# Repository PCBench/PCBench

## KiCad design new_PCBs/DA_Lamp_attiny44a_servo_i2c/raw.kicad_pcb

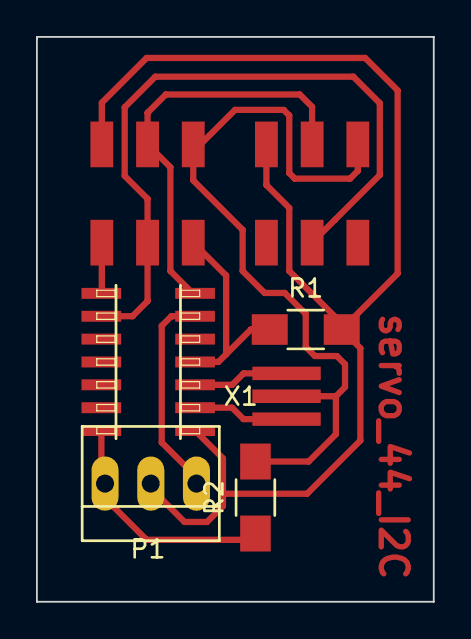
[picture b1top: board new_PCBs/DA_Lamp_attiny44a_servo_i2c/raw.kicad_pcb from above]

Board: 2 copper layers, 22.0 x 31.4 mm, 7 parts (0 on the bottom side), 9 nets.

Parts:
IC1: ATTINY44A-SS; fab-SOIC14
M1: AVRISP & I2C; fab-2X03SMD
M2: I2C; fab-2X03SMD
P1: CONN_01X03; PINHEAD1-3
R1: 10k; R_1206_HandSoldering
R2: 0; R_1206_HandSoldering
X1: CRYSTAL_SMD; Crystal_XC1109CT-ND

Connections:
+5V: IC1.1, M1.2, M2.2, P1.2, R1.2
/PA4: IC1.9, M1.3, M2.3
/PA5: IC1.8, M1.1
/PA6: IC1.7, M1.4, M2.4
/PA7: IC1.6, P1.1
/PB3: IC1.4, M1.5, R1.1
GND: IC1.14, M1.6, M2.6, P1.3, R2.1, R2.2, X1.2
unnamed: IC1.2, X1.3
unnamed: IC1.3, X1.1

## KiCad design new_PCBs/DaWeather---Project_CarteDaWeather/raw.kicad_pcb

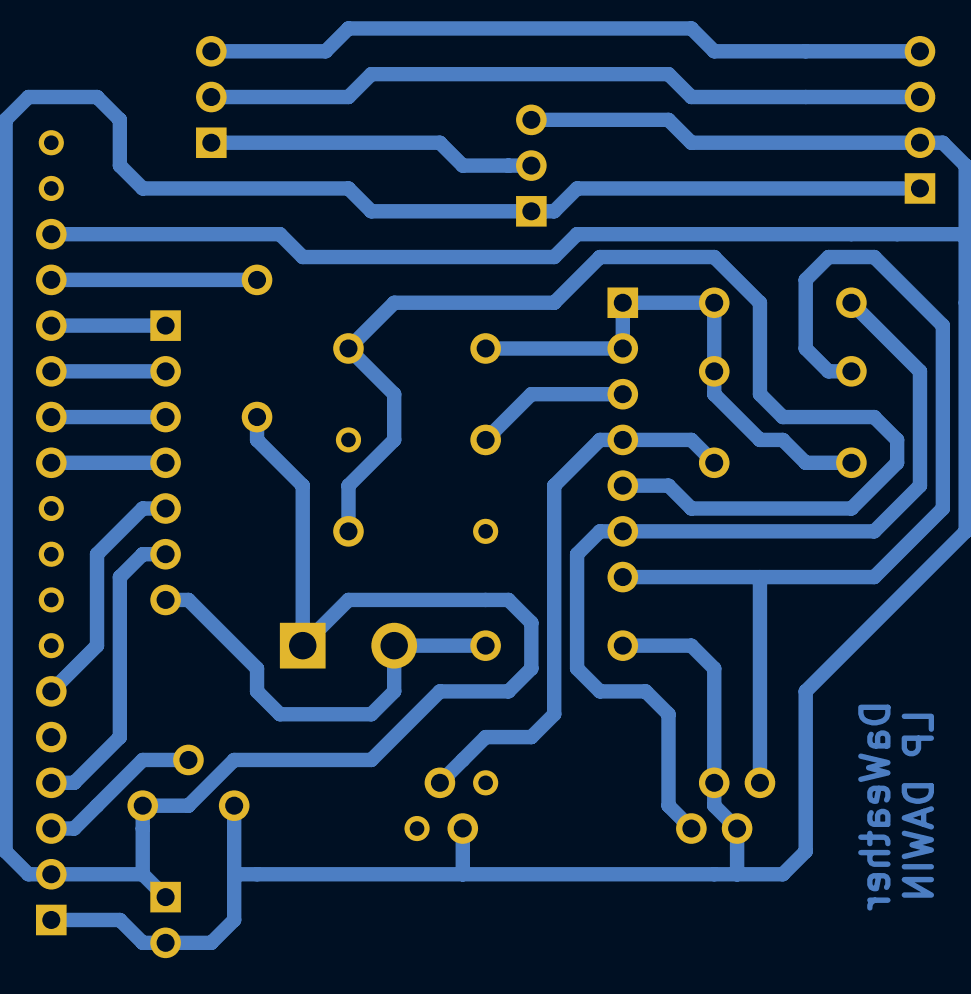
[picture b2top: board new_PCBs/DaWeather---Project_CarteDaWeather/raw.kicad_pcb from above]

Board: 2 copper layers, 18 parts (0 on the bottom side), 20 nets.

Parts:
+1: CONN_2; SIL-2
ARD1: CONN_3; SIL-3
BMP180: CONN_4; SIL-4
BP1: SW_PUSH; SW_PUSH_SMALL
CONN1, CONN2: CONN_7; SIL-7
JP1: CONN_2; bornier2
P1: CONN LCD; SIL-18
R1, R2, R3, R4, R5: 10 K; R3
R6: 220; R3
RJ1, RJ2: RJ-11; scenix4-RJ-11
RV1: POT; RV2
TMP36: CONN_3; SIL-3

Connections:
unnamed: CONN2.6, R3.2, RJ2.2
unnamed: BP1.2, CONN2.5, R1.2
unnamed: CONN2.7, R4.2, RJ2.5
unnamed: CONN2.4, R2.2, RJ1.3
unnamed: BP1.1, CONN2.3
unnamed: +1.1, BMP180.1, JP1.1, P1.2, R6.1, RV1.1, TMP36.1
unnamed: ARD1.1, TMP36.2
unnamed: ARD1.2, BMP180.3
unnamed: ARD1.3, BMP180.4
unnamed: CONN1.6, P1.4
unnamed: P1.15, R6.2
unnamed: CONN1.7, JP1.2, R5.2
unnamed: CONN1.1, P1.14
unnamed: CONN1.2, P1.13
unnamed: CONN1.4, P1.11
unnamed: CONN2.1, CONN2.2, R1.1, R2.1, R3.1, R4.1
unnamed: P1.3, RV1.2
unnamed: +1.2, BMP180.2, P1.1, P1.5, P1.16, R5.1, RJ1.4, RJ2.3, RJ2.4, RV1.3, TMP36.3
unnamed: CONN1.5, P1.6
unnamed: CONN1.3, P1.12

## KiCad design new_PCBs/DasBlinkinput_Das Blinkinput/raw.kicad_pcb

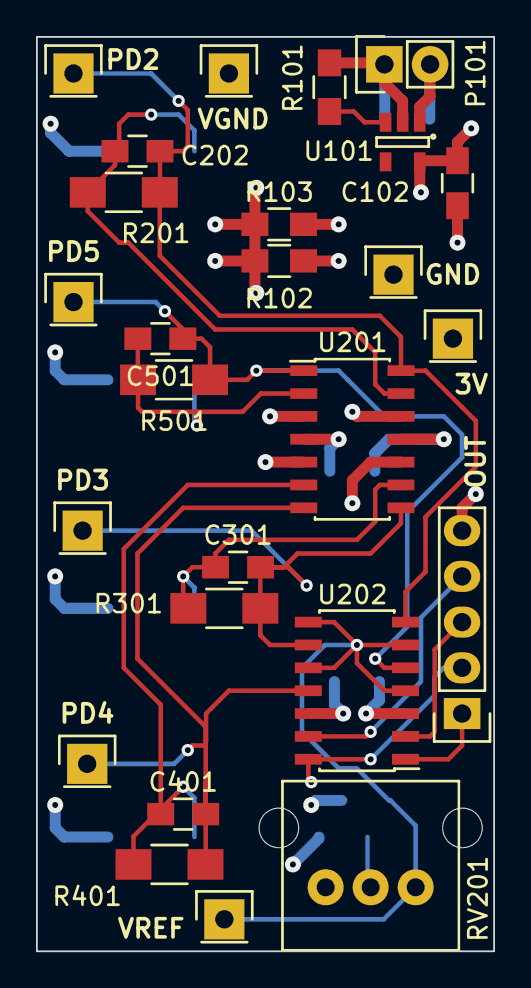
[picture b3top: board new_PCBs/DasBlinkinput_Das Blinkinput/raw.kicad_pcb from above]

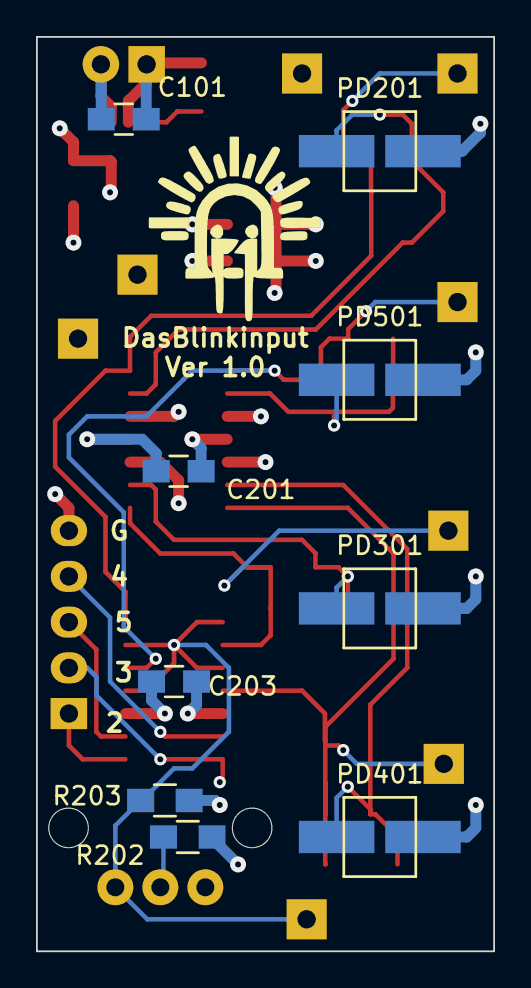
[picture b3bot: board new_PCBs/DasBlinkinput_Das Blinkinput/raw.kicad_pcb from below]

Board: 4 copper layers, 25.4 x 50.8 mm, 35 parts (9 on the bottom side), 19 nets.

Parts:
C101, C102: 1U; C_0805_HandSoldering
C201, C203: .1U; C_0805_HandSoldering
C202, C301, C401, C501: 100p; C_0805_HandSoldering
P101: CONN_01X02; Pin_Header_Straight_1x02
P102, P103, P104, P106, P201, P301, P401, P501: CONN_01X01; Pin_Header_Straight_1x01
P105: CONN_01X05; Pin_Header_Straight_1x05
PD201, PD301, PD401, PD501: VBPW34SR; VPW34SR*
R101: 0; R_0805_HandSoldering
R102, R103, R202, R203: 10K; R_0805_HandSoldering
R201, R301, R401, R501: 1MEG; R_1206_HandSoldering
RV201: POT; P090L-02F25BR10K
U101: LP2980IM5-3.0/NOPB; SOT-23-5
U201: MCP6404; SOIC-14_3.9x8.7mm_Pitch1.27mm
U202: LM339; SOIC-14_3.9x8.7mm_Pitch1.27mm

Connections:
3V: C102.1, C201.2, C203.2, P103.1, R102.1, R203.2, U101.5, U201.4, U202.3
/Channel1Photodetect/PD2: P105.1, U202.1
/Channel2Photodetect/PD3: P105.2, U202.14
/Channel2Photodetect/REF_IN: P106.1, R202.2, RV201.3, U202.4, U202.6, U202.8, U202.10
/Channel3Photodetect/PD5: P105.3, U202.2
/Channel4Photodetect/PD4: P105.4, U202.13
GND: C101.2, C102.2, C201.1, C203.1, P101.1, P104.1, P105.5, R101.2, R103.2, R202.1, U101.2, U201.11, U202.12
unnamed: C101.1, P101.2, U101.1
unnamed: C202.1, P201.1, R201.1, U201.14, U202.7
unnamed: C202.2, PD201.2, R201.2, U201.13
unnamed: C301.1, P301.1, R301.1, U201.8, U202.9
unnamed: C301.2, PD301.2, R301.2, U201.9
unnamed: C401.1, P401.1, R401.1, U201.7, U202.11
unnamed: C401.2, PD401.2, R401.2, U201.6
unnamed: C501.1, P501.1, R501.1, U201.1, U202.5
unnamed: C501.2, PD501.2, R501.2, U201.2
unnamed: R101.1, U101.3
unnamed: R203.1, RV201.2
VGND: P102.1, PD201.1, PD301.1, PD401.1, PD501.1, R102.2, R103.1, U201.3, U201.5, U201.10, U201.12

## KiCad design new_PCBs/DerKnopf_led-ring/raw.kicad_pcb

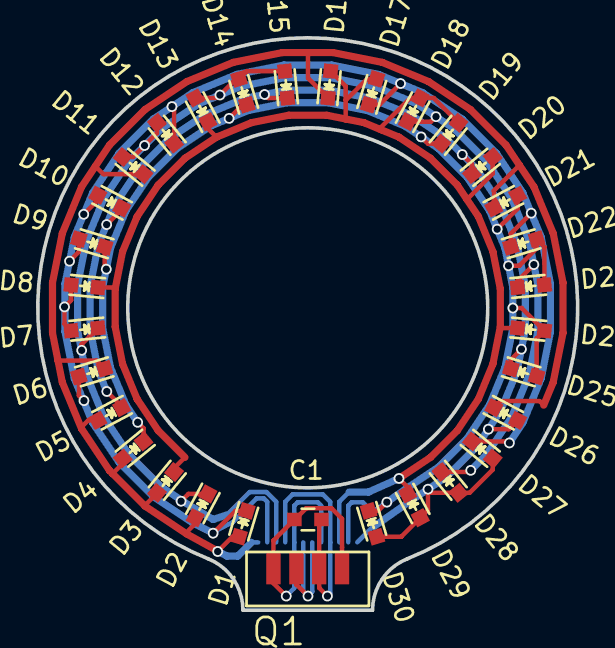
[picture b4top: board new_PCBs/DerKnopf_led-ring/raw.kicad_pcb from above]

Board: 2 copper layers, 30.0 x 31.8 mm, 33 parts (1 on the bottom side), 9 nets.

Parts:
C1: 100n; C_0603
D1, D2, D3, D4, D5, D6, D7, D8, D9, D10, D11, D12, D13, D14, D15, D16, D17, D18, D19, D20, D21, D22, D23, D24, D25, D26, D27, D28, D29, D30: LED; LED_0603
P1: CONN_01X12; FlatFlex
Q1: TSOP75338; TSOP75xx

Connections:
/GND: C1.2, P1.5, P1.8, Q1.1, Q1.4
/IR-signal: P1.6, P1.7, Q1.3
/VCC: C1.1, P1.4, P1.9, Q1.2
A: D1.2, D2.2, D3.2, D4.2, D5.2, D6.1, D11.1, D16.1, D21.1, D26.1, P1.1
B: D1.1, D6.2, D7.2, D8.2, D9.2, D10.2, D12.1, D17.1, D22.1, D27.1, P1.2
C: D2.1, D7.1, D11.2, D12.2, D13.2, D14.2, D15.2, D18.1, D23.1, D28.1, P1.3
D: D3.1, D8.1, D13.1, D16.2, D17.2, D18.2, D19.2, D20.2, D24.1, D29.1, P1.10
E: D4.1, D9.1, D14.1, D19.1, D21.2, D22.2, D23.2, D24.2, D25.2, D30.1, P1.11
F: D5.1, D10.1, D15.1, D20.1, D25.1, D26.2, D27.2, D28.2, D29.2, D30.2, P1.12

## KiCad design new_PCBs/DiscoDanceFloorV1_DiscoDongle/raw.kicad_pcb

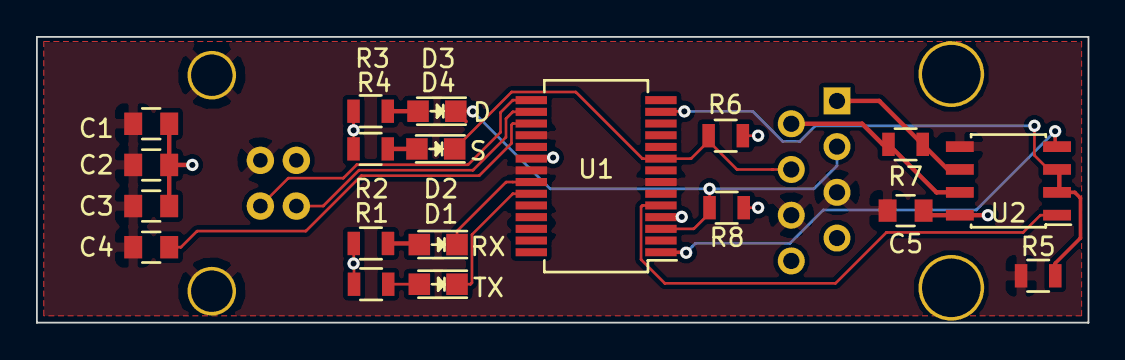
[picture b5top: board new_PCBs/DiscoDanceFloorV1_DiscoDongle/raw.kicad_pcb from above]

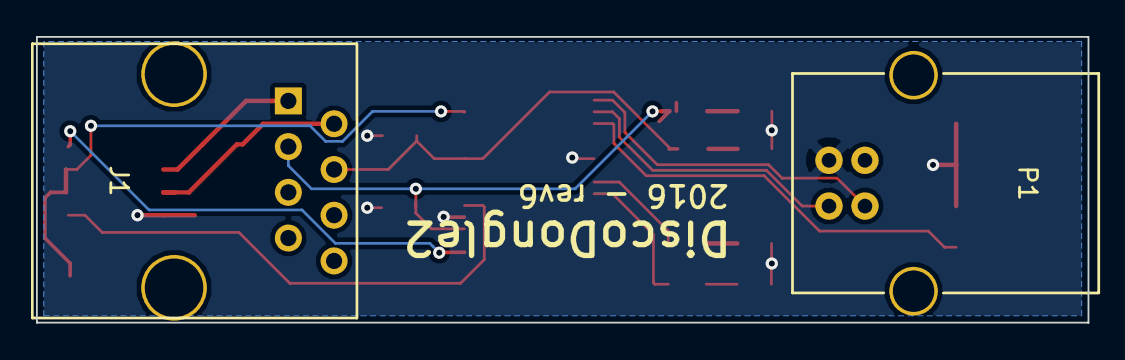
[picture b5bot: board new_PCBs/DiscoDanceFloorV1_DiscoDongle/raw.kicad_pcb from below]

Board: 2 copper layers, 58.4 x 15.9 mm, 21 parts (2 on the bottom side), 18 nets.

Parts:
C1, C4, C5: 100nF; C_0805
C2: 4.7uF; C_0805
C3: 10nF; C_0805
D1: TX; LED_0805
D2: RX; LED_0805
D3: D; LED_0805
D4: S; LED_0805
J1: RJ45; RJ45_8
P1: USB_B
R1, R2, R3, R4: 200; R_0805
R5, R6, R8: 20k; R_0805
R7: 120; R_0805
U1: FT232RL; SSOP-28_5.3x10.2mm_Pitch0.65mm
U2: ISL81487E; SOIC-8_3.9x4.9mm_Pitch1.27mm

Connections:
+5V: C1.1, C2.1, C3.1, C5.1, P1.1, R1.1, R2.1, R3.1, R4.1, R6.1, R8.1, U1.4, U1.20, U2.8
Daisy: D3.1, J1.3, R8.2, U1.3
GND: C1.2, C2.2, C3.2, C4.2, C5.2, J1.5, J1.6, P1.4, P1.5, R5.2, U1.7, U1.18, U1.21, U1.25, U1.26, U2.5
unnamed: C4.1, U1.17
unnamed: D1.2, R1.2
unnamed: D2.2, R2.2
unnamed: D3.2, R3.2
unnamed: D4.2, R4.2
unnamed: J1.1, R7.2, U2.6
unnamed: J1.2, R7.1, U2.7
unnamed: P1.2, U1.16
unnamed: P1.3, U1.15
unnamed: R5.1, U1.13, U2.2, U2.3
unnamed: U1.1, U2.4
unnamed: U1.5, U2.1
RXLED: D2.1, U1.22
Signal: D4.1, J1.4, R6.2, U1.9
TXLED: D1.1, U1.23

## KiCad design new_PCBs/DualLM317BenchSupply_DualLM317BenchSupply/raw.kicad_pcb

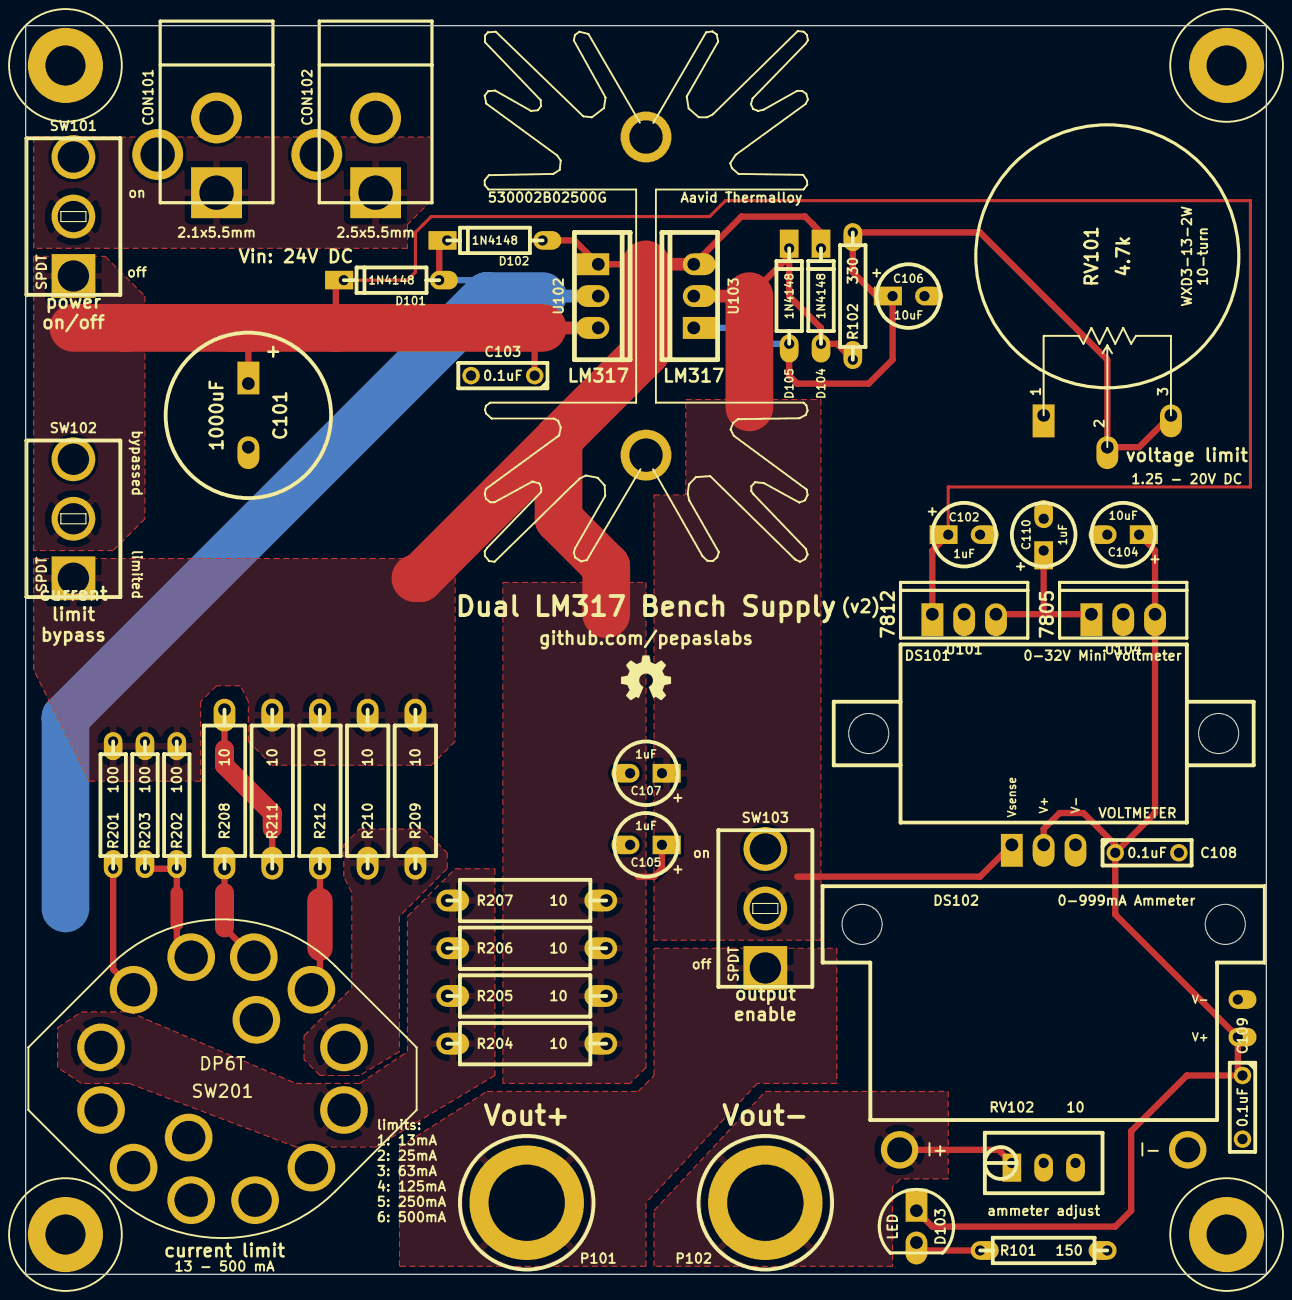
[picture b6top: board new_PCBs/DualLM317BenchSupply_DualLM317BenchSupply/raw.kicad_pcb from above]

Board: 2 copper layers, 99.1 x 99.7 mm, 50 parts (0 on the bottom side), 19 nets.

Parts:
C101: 1000uF; ELCAP_20_52_V
C102, C105, C107, C110: 1uF; ELCAP_10_20_V
C103, C108, C109: 0.1uF; C2
C104, C106: 10uF; ELCAP_10_20_V
CON101: BARREL_JACK; BARREL_JACK_21x55
CON102: BARREL_JACK; BARREL_JACK_25x55
D101, D102, D104, D105: 1N4148; DIODE_3
D103: LED; LED_5MM
DS101: VOLTMETER; DVM036A
DS102: AMMETER_V; EBAY_AMMETER
H101, H102, H103, H104: HOLE; hole_M3
H***: 530002B02500G
P101: Vout+; Banana_A
P102: Vout-; Banana_A
R101: 150; R_AXIAL_0W25
R102: 330; R_AXIAL_0W25
R201, R202, R203: 100; R_AXIAL_0W25
R204, R205, R206, R207, R208, R209, R210, R211, R212: 10; R_AXIAL_0W5
RV101: 4.7k; WXD3-13-2W_A
RV102: 10; 3296W
SW101, SW102, SW103: SPDT; M2012SS1W01
SW201: DP6T; G3SR022-R
U101: 7812; TO-220_V_069B
U102, U103: LM317; TO-220_V_069B
U104: 7805; TO-220_V_069B

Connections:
5V: C104.1, C108.1, C109.1, D103.1, DS101.2, DS102.3, U104.3
12V: C110.1, U101.3, U104.1
/current_limit_r/R_LIM+: D101.1, D102.2, SW201.1, SW201.8, U102.2
/current_limit_r/R_LIM-: C105.1, D102.1, D104.2, R201.2, R202.2, R203.2, R204.2, R205.2, R206.2, R207.2, R209.2, R210.2, R211.2, R212.2, SW102.1, U102.1, U103.3
GND: C101.2, C102.2, C103.2, C104.2, C105.2, C106.2, C107.2, C108.2, C109.2, C110.2, CON101.2, CON101.3, CON102.2, CON102.3, DS101.3, DS102.2, DS102.4, R101.2, RV101.1, RV102.2, RV102.3, U101.2, U104.2
unnamed: C107.1, D104.1, D105.2, DS101.1, R102.1, SW103.2, U103.2
unnamed: C106.1, D105.1, R102.2, RV101.2, RV101.3, U103.1
unnamed: P101.1, SW103.1
unnamed: DS102.1, P102.1, RV102.1
unnamed: D103.2, R101.1
unnamed: CON101.1, CON102.1, SW101.2
unnamed: C101.1, C102.1, C103.1, D101.2, SW101.1, SW102.2, U101.1, U102.3
unnamed: R209.1, R210.1, SW201.6, SW201.13
unnamed: R204.1, R205.1, R206.1, R207.1, SW201.7, SW201.14
unnamed: R208.2, R211.1
unnamed: R212.1, SW201.5
unnamed: R208.1, SW201.4
unnamed: R201.1, SW201.2
unnamed: R202.1, R203.1, SW201.3

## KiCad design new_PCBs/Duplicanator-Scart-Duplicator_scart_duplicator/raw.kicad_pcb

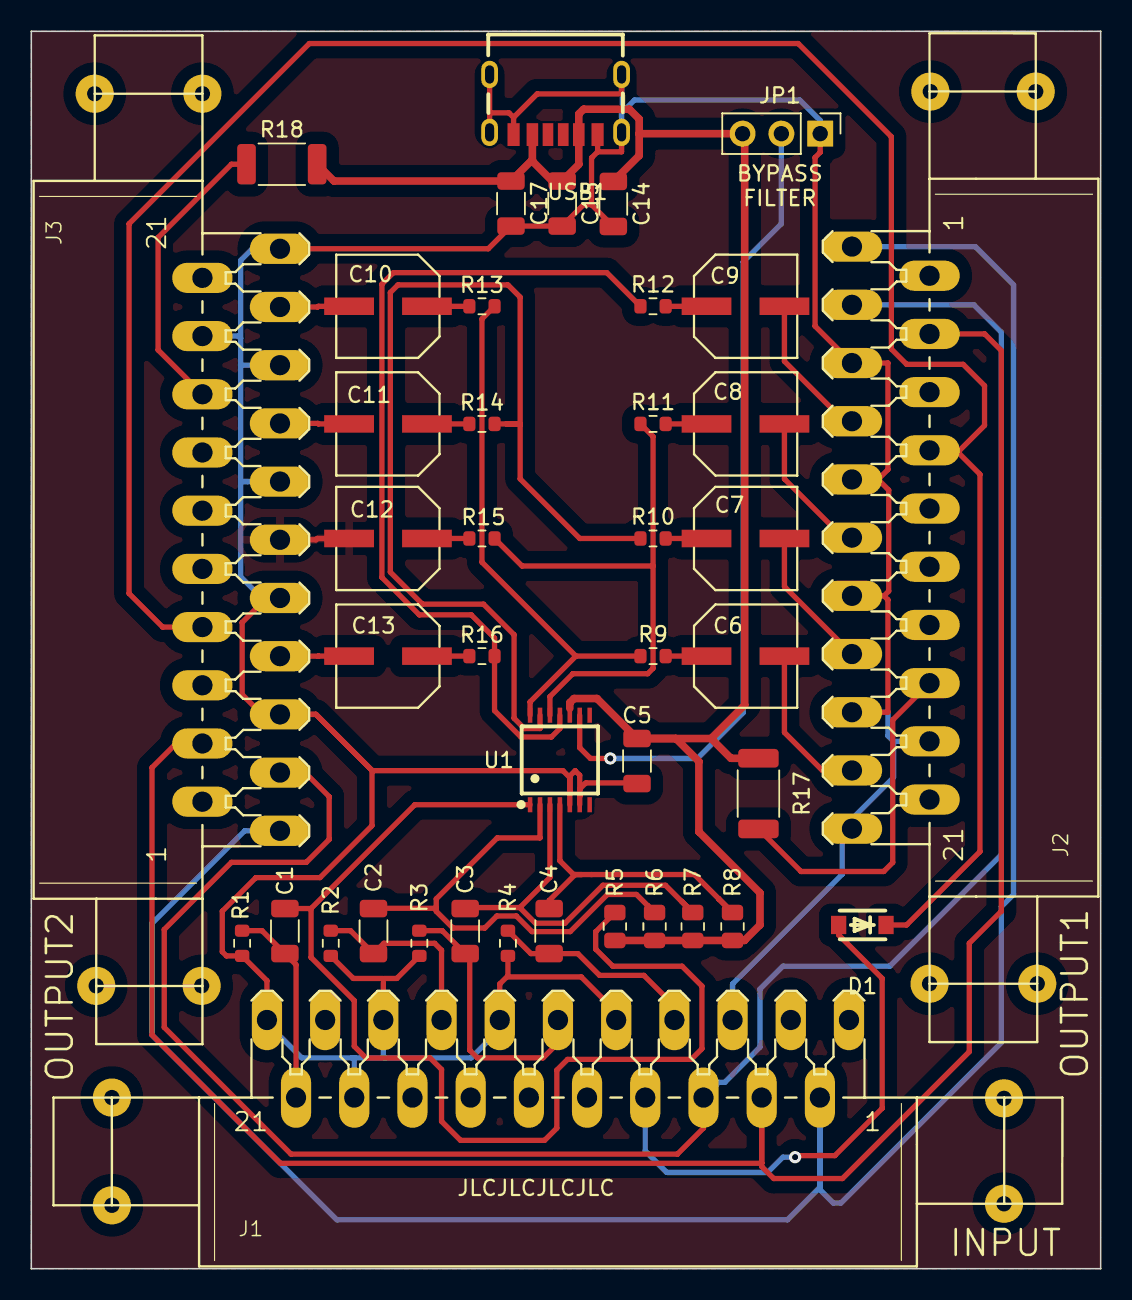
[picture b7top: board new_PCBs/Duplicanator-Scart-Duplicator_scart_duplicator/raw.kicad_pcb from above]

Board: 2 copper layers, 70.0 x 81.0 mm, 42 parts (1 on the bottom side), 38 nets.

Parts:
C1, C2, C3, C4, C5, C17: 0.1u; C_1206_3216Metric
C6, C7, C8, C9, C10, C11, C12, C13: 330u; CAP-SMD_BD6.3-L6.6-W6.6-LS7.2-R-RD
C14: 10n; C_1206_3216Metric
C15: 10u; C_1206_3216Metric
D1: SOD4007; SOD-123F_L2.8-W1.8-LS3.7-RD
G1: LOGO; LogoKabuki
J1: INPUT; SCART-F_solder_pads
J2: OUTPUT1; SCART-F_solder_pads
J3: OUTPUT2; SCART-F_solder_pads
JP1: FILTER_BYPASS; PinHeader_1x03_P2.54mm_Vertical
R1, R2, R3, R4, R9, R10, R11, R12, R13, R14, R15, R16: 75; R_0603_1608Metric
R5, R6, R7, R8: 5.36M; R_0805_2012Metric
R17, R18: 180; R_2010_5025Metric
U1: THS7374IPWR; TSSOP-14_L5.0-W4.4-P0.65-LS6.5-BL
USB1: USB-312; USB-C-SMD_10P-P1.00-L6.8-W8.9

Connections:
+5V: C5.1, C14.1, C15.1, C17.1, JP1.3 (B), R5.2, R6.2, R7.2, R8.2, R17.2, R18.2, U1.10 (VS+), USB1.2 (B9_VBUS), USB1.5 (A9_VBUS)
/AUDIO_GND: J1.4, J2.4, J3.4
/AUDIO_LEFT: J1.6, J2.3, J3.3
/AUDIO_RIGHT: J1.2, J2.1, J3.1
/B_IN: C4.1, J1.7, R4.1
/B_OUT1: C9.2, J2.7
/B_OUT2: C13.2, J3.7
/CSYNC_IN: C1.1, J1.20, R1.1
/CSYNC_OUT1: C6.2, J2.19
/CSYNC_OUT2: C10.2, J3.19
/G_IN: C3.1, J1.11, R3.1
/G_OUT1: C8.2, J2.11
/G_OUT2: C12.2, J3.11
/R_IN: C2.1, J1.15, R2.1
/R_OUT1: C7.2, J2.15
/R_OUT2: C11.2, J3.15
/SWITCHING: D1.1 (C), J2.8, J3.8
GND: C5.2, C14.2, C15.2, C17.2, J1.5, J1.9, J1.13, J1.17, J1.18, J1.21, J2.5, J2.9, J2.13, J2.17, J2.18, J2.21, J3.5, J3.9, J3.13, J3.17, J3.18, J3.21, JP1.1 (A), R1.2, R2.2, R3.2, R4.2, U1.5 (GND), U1.6 (DISABLE), USB1.0, USB1.1 (B12_GND), USB1.6 (A12_GND)
unnamed: C6.1, R9.2
unnamed: C7.1, R10.2
unnamed: C8.1, R11.2
unnamed: C9.1, R12.2
unnamed: C10.1, R13.2
unnamed: C11.1, R14.2
unnamed: C12.1, R15.2
unnamed: C13.1, R16.2
unnamed: D1.2 (A), J1.8
unnamed: J2.16, R17.1
unnamed: J3.16, R18.1
unnamed: JP1.2 (C), U1.9 (BYPASS)
unnamed: C1.2, R5.1, U1.1 (CH1IN)
unnamed: R9.1, R13.1, U1.14 (CH1OUT)
unnamed: C2.2, R6.1, U1.2 (CH2IN)
unnamed: R10.1, R14.1, U1.13 (CH2OUT)
unnamed: C3.2, R7.1, U1.3 (CH3IN)
unnamed: R11.1, R15.1, U1.12 (CH3OUT)
unnamed: C4.2, R8.1, U1.4 (CH4IN)
unnamed: R12.1, R16.1, U1.11 (CH4OUT)
